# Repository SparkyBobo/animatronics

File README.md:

# animatronics
An animatronic framework for CircuitPython.

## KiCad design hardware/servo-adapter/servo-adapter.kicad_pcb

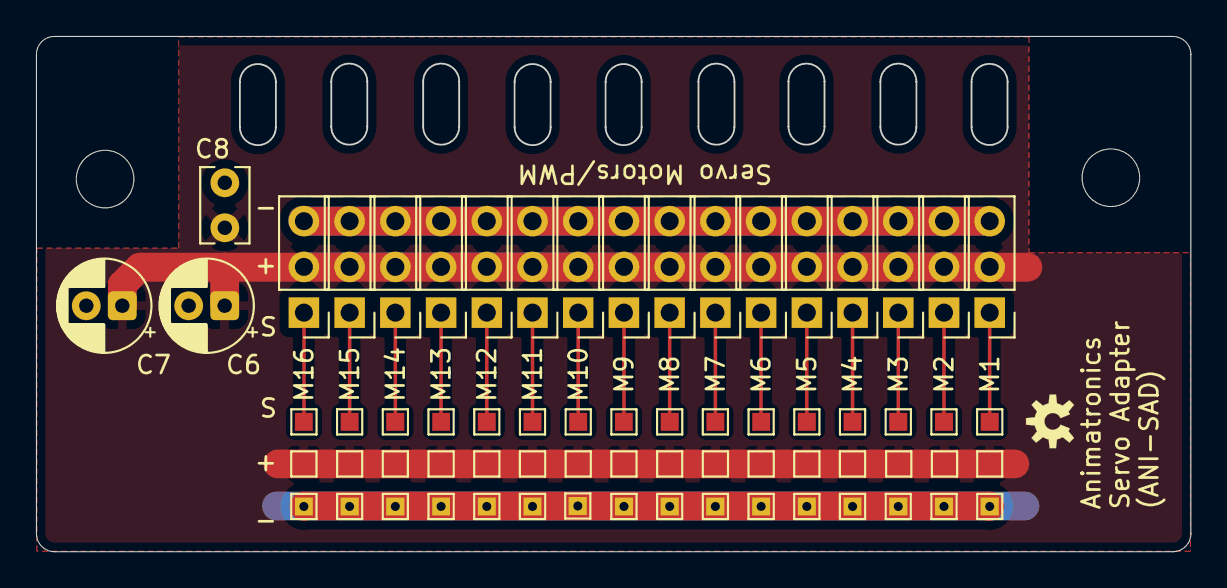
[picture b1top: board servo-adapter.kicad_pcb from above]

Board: 2 copper layers, 64.1 x 28.6 mm, 69 parts (0 on the bottom side), 18 nets.

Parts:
C6, C7: 100uf; CP_Radial_D5.0mm_P2.00mm
C8: 0.1uF; C_Rect_L4.0mm_W2.5mm_P2.50mm
H1, H2: MountingHole; MountingHole_3.2mm_M3
J1, J2, J3, J4, J5, J6, J7, J8, J9, J10, J11, J12, J13, J14, J15, J16, J17, J18, J19, J20, J21, J22, J23, J24, J25, J26, J27, J28, J29, J30, J31, J32: Servo M1; TestPoint_Pad_1.0x1.0mm
J33, J34, J35, J36, J37, J38, J39, J40, J41, J42, J43, J44, J45, J46, J47, J48: Servo M1; TestPoint_THTPad_1.0x1.0mm_Drill0.5mm
M1, M2, M3, M4, M5, M6, M7, M8, M9, M10, M11, M12, M13, M14, M15, M16: Motor_Servo; PinHeader_1x03_P2.54mm_Vertical

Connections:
+5VA: C6.1, C7.1, C8.1, J17.1, J18.1, J19.1, J20.1, J21.1, J22.1, J23.1, J24.1, J25.1, J26.1, J27.1, J28.1, J29.1, J30.1, J31.1, J32.1, M1.2 (+), M2.2 (+), M3.2 (+), M4.2 (+), M5.2 (+), M6.2 (+), M7.2 (+), M8.2 (+), M9.2 (+), M10.2 (+), M11.2 (+), M12.2 (+), M13.2 (+), M14.2 (+), M15.2 (+), M16.2 (+)
GND: C6.2, C7.2, C8.2, J33.1, J34.1, J35.1, J36.1, J37.1, J38.1, J39.1, J40.1, J41.1, J42.1, J43.1, J44.1, J45.1, J46.1, J47.1, J48.1, M1.3 (-), M2.3 (-), M3.3 (-), M4.3 (-), M5.3 (-), M6.3 (-), M7.3 (-), M8.3 (-), M9.3 (-), M10.3 (-), M11.3 (-), M12.3 (-), M13.3 (-), M14.3 (-), M15.3 (-), M16.3 (-)
unnamed: J1.1, M1.1 (PWM)
unnamed: J2.1, M2.1 (PWM)
unnamed: J3.1, M3.1 (PWM)
unnamed: J4.1, M4.1 (PWM)
unnamed: J5.1, M5.1 (PWM)
unnamed: J6.1, M6.1 (PWM)
unnamed: J7.1, M7.1 (PWM)
unnamed: J8.1, M8.1 (PWM)
unnamed: J9.1, M9.1 (PWM)
unnamed: J10.1, M10.1 (PWM)
unnamed: J11.1, M11.1 (PWM)
unnamed: J12.1, M12.1 (PWM)
unnamed: J13.1, M13.1 (PWM)
unnamed: J14.1, M14.1 (PWM)
unnamed: J15.1, M15.1 (PWM)
unnamed: J16.1, M16.1 (PWM)

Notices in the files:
hardware/servo-adapter/servo-adapter.kicad_pcb:
https://creativecommons.org/licenses/by-sa/4.0
Released under the Creative Commons Attribution Share-Alike 4.0 License
